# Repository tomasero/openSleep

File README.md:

# OpenSleep

The development of the hardware and software for this system started and most of it was done during my first semester at the Fluid Interfaces Group of the MIT Media Lab. This technology was used for many projects, [Dormio](https://www.media.mit.edu/projects/sleep-creativity/overview/) being the most notable. This project is part of a larger iniatiative called Engineering Dreams, which seeks to build technology that interfaces with the sleeping mind.

----

# The following is deprecated. We are about to release a new tutorial. Thanks for your patience!

----

## Hardware

### Components

| Qty | Value | Device  | Where |
|:---:|:-----:| -------:| ----- |
|  2  | .1uF  | CAP_CERAMIC0603 | Digikey: [399-1095-1-ND](https://www.digikey.com/product-detail/en/kemet/C0603C104K8RACTU/399-1095-1-ND/411370) |
|  1  |  1uF  | CAP_CERAMIC0603 | Digikey: [399-5090-1-ND](https://www.digikey.com/product-detail/en/kemet/C0603C105K4PACTU/399-5090-1-ND/1465624) | 
|  1  |  1K   | R-US_0503       | Digikey: [YAG1237CT-ND](https://www.digikey.com/product-detail/en/yageo/RT0603BRD071KL/YAG1237CT-ND/4340590) | 
|  2  | 100K  | R-US_R0603      | Digikey: [YAG1235CT-ND](https://www.digikey.com/product-detail/en/yageo/RT0603BRD07100KL/YAG1235CT-ND/4340588) |
|  3  |  1x2  | 1X2-SMD-HEADER  | Digikey: [S1113E-36-ND](https://www.digikey.com/product-detail/en/sullins-connector-solutions/GEC36SBSN-M89/S1113E-36-ND/862247) |
|  1  |  1x3  | 1X3-SMD-HEADER  | Digikey: [S1113E-36-ND](https://www.digikey.com/product-detail/en/sullins-connector-solutions/GEC36SBSN-M89/S1113E-36-ND/862247) |
|  1  |  1x5  | 1X5-SMD-HEADER  | Digikey: [S1113E-36-ND](https://www.digikey.com/product-detail/en/sullins-connector-solutions/GEC36SBSN-M89/S1113E-36-ND/862247) |
|  1  |       | RFD22301        | Digikey: [1562-1016-ND](https://www.digikey.com/product-detail/en/rf-digital-corporation/RFD22301/1562-1016-ND/5056363) |
|  1  | SPDT  | SLIDE-SWITCH    | Digikey: [401-2014-1-ND](https://www.digikey.com/product-detail/en/c-k/AYZ0103AGRLC/401-2014-1-ND/1640123) |
|  1  | Color | LED-1206-SMD    | Digikey: [516-1436-1-ND](https://www.digikey.com/product-detail/en/broadcom-limited/HSMR-C150/516-1436-1-ND/637760) |
|  1  |       | HR-SENSOR       | Adafruit: [1093](https://www.adafruit.com/product/1093) |
|  1  |       | FLEX-SENSOR     | Adafruit: [1070](https://www.adafruit.com/product/1070) |
|  2  |       | EDA-ELECTRODE-CABLE | [OpenBCI](https://shop.openbci.com/collections/frontpage/products/emg-ecg-snap-electrode-cables?variant=32372786958) |
| 2   |       | EDA-ELECTRODE   | [OpenBCI](https://shop.openbci.com/collections/frontpage/products/skintact-f301-pediatric-foam-solid-gel-electrodes-30-pack?variant=29467659395) |

### PCB

#### Design

##### Schematic

##### Layout 

#### Fabrication

You can either mill the PCB yourself using a CNC mill, or buy one from a PCB manufacturer.

##### Mill it

The original PCB for Doormio was made using a Roland MDX-20. All the PNG files used to mill the board can be found in the following folder:

    /hardware/PNG

##### Order it

[Oshpark!](https://oshpark.com/shared_projects/I6SkyNbt)

## Software

### Web App

Run the app:

    node web_app/app.js

Open the app:

    http://localhost:3000

### Mobile App

## Acknowledgements 

[Adam Horowitz](https://www.media.mit.edu/people/adamjhh/overview/) led the experiment design and execution to validate the system, [Oscar Rosello](https://www.media.mit.edu/people/rosello/overview/) the interaction and form factor, and  [Eyal Perry](https://www.media.mit.edu/people/eyalp/overview/) the iOS app development, signal processing and classification (and great mustache). [Matthew Ha](https://github.com/matthewha123) continued the development of the iOS 
    app and analysis of biosignals for sleep staging.

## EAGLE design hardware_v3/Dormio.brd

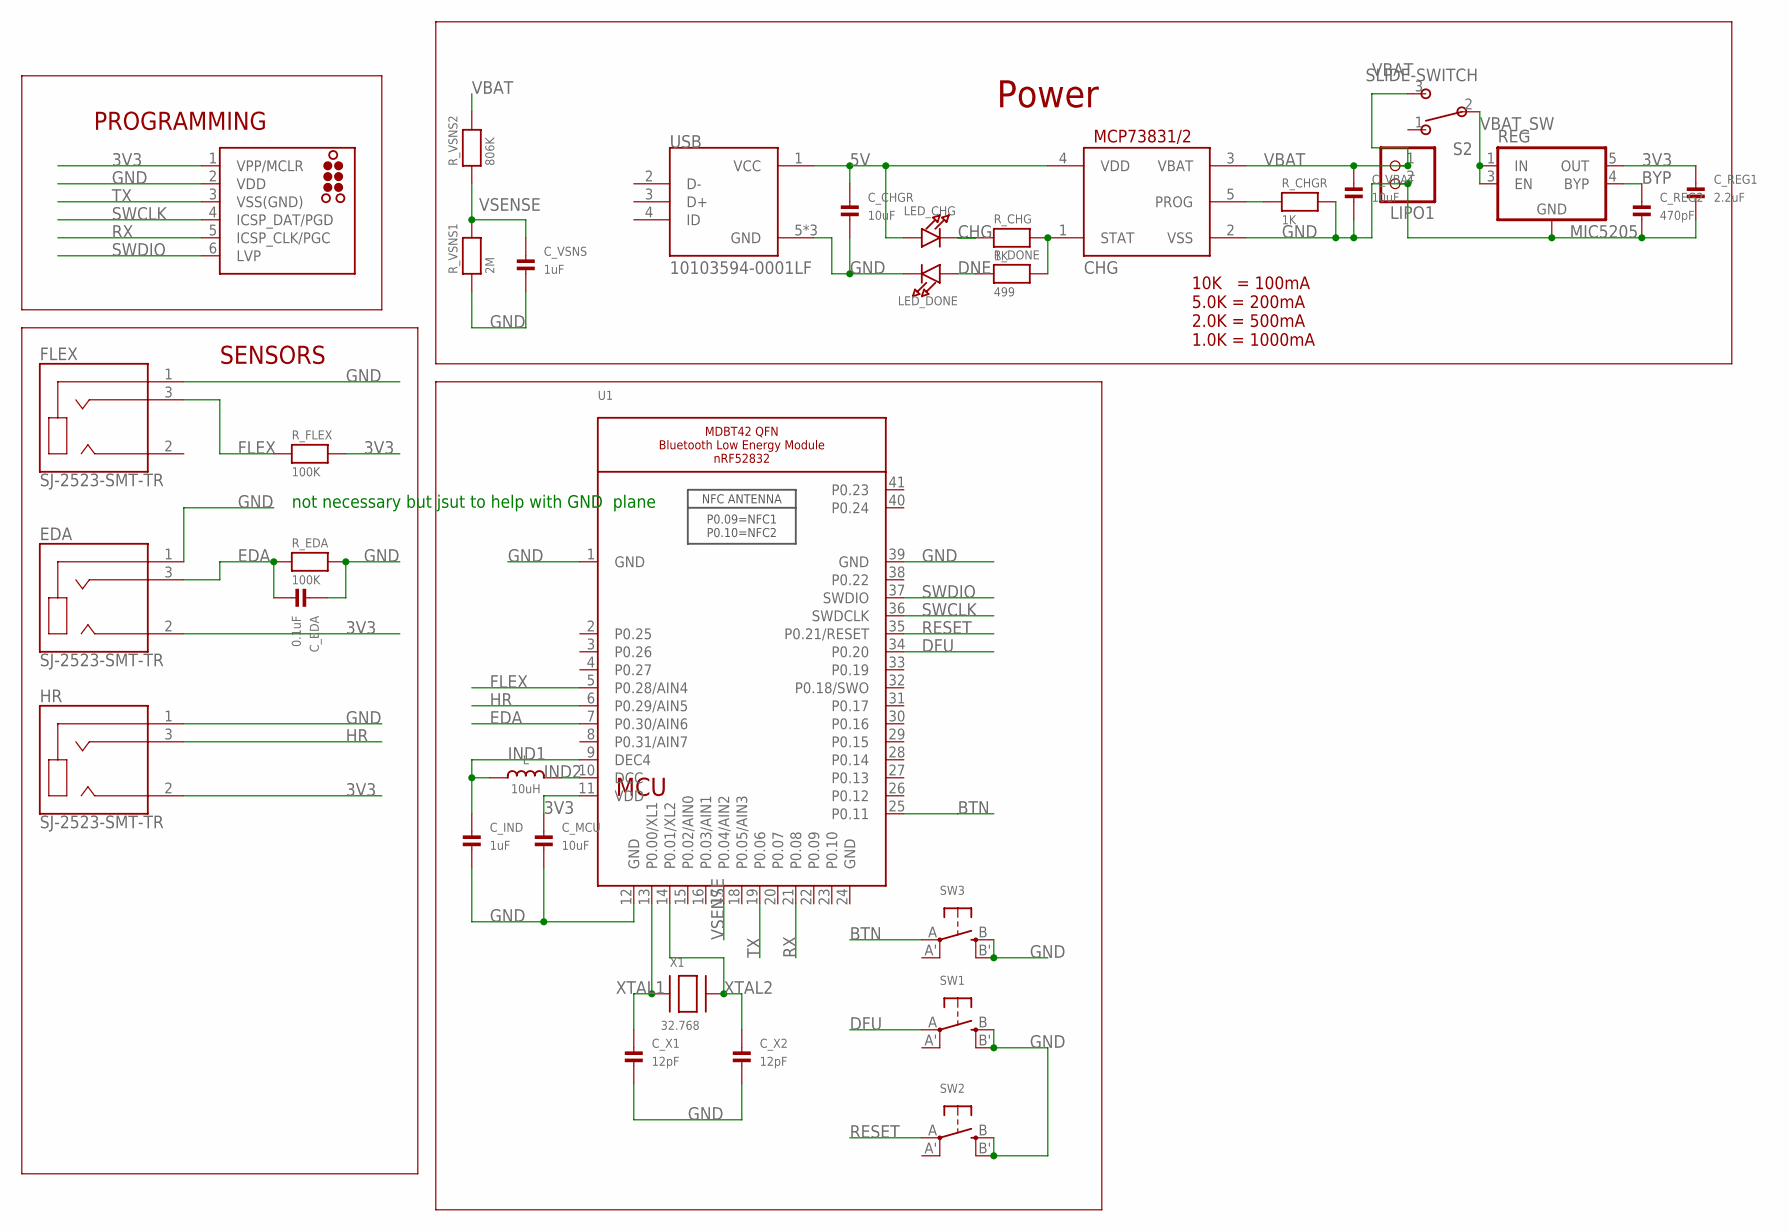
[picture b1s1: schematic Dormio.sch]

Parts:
CHG: MCP73831/OT; SOT23-5L
C_CHGR: 10uF; 1206
C_EDA: 0.1uF; 1206
C_IND: 1uF; 1206
C_MCU: 10uF; 1206
C_REG1: 2.2uF; 1206
C_REG2: 470pF; 1206
C_VBAT: 10uF; 1206
C_VSNS: 1uF; 1206
C_X1, C_X2: 12pF; 1206
EDA: SJ-2523-SMT-TR; CUI_SJ-2523-SMT-TR
FLEX: SJ-2523-SMT-TR; CUI_SJ-2523-SMT-TR
HR: SJ-2523-SMT-TR; CUI_SJ-2523-SMT-TR
J1: TC2030-MCP-NL
L: 10uH; MICROBUILDER_INDUCTOR_1007
LED_CHG: LED1206; CHIPLED_1206
LED_DONE: LED1206; CHIPLED_1206
LIPO1: JST_2PIN-SMT-RA; JST-PH-2-SMT-RA
REG: MIC5205; SOT23-5
R_CHG: 1K; 1206
R_CHGR: 1K; 1206
R_DONE: 499; 1206
R_EDA: 100K; 1206
R_FLEX: 100K; 1206
R_VSNS1: 2M; 1206
R_VSNS2: 806K; 1206
S2: SLIDE-SWITCH; AYZ0102AGRLC
SW1, SW2, SW3: MICROBUILDER_SWITCH_TACT_SMT4.6X2.8; MICROBUILDER_BTN_KMR2_4.6X2.8
U1: MICROBUILDER_NRF52832_MODULE_MDBT42; MICROBUILDER_BLE_MODULE_RAYTAC_MDBT42
USB: 10103594-0001LF; FCI_10103594-0001LF
X1: 32.768; XTAL3215

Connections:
3V3: C_MCU.1, C_REG1.1, EDA.2, HR.2, J1.1 (VPP/MCLR), REG.5 (OUT), R_FLEX.2, U1.11 (VDD)
5V: CHG.4 (VDD), C_CHGR.1, LED_CHG.A, USB.1 (VCC)
BTN: SW3.A, U1.25 (P0.11)
BYP: C_REG2.1, REG.4 (BYP)
CHG: LED_CHG.C, R_CHG.1
DFU: SW1.A, U1.34 (P0.20)
DNE: LED_DONE.A, R_DONE.1
EDA: C_EDA.2, EDA.3, R_EDA.1, U1.7 (P0.30/AIN6)
FLEX: FLEX.3, R_FLEX.1, U1.5 (P0.28/AIN4)
GND: CHG.2 (VSS), C_CHGR.2, C_EDA.1, C_IND.2, C_MCU.2, C_REG1.2, C_REG2.2, C_VBAT.2, C_VSNS.2, C_X1.2, C_X2.2, EDA.1, FLEX.1, HR.1, J1.2 (VDD), LED_DONE.C, LIPO1.2 (1), REG.2 (GND), R_CHGR.2, R_EDA.2, R_VSNS1.1, SW1.B (S), SW1.B' (S1), SW2.B (S), SW2.B' (S1), SW3.B (S), SW3.B' (S1), U1.1 (GND), U1.12 (GND), U1.39 (GND), USB.5 (GND), USB.P3 (GND), USB.P4 (GND)
HR: HR.3, U1.6 (P0.29/AIN5)
IND1: C_IND.1, L.P$1 (1), U1.9 (DEC4)
IND2: L.P$2 (2), U1.10 (DCC)
PROG: CHG.5 (PROG), R_CHGR.1
RESET: SW2.A, U1.35 (P0.21/RESET)
RX: J1.5 (ICSP_CLK/PGC), U1.21 (P0.08)
STAT: CHG.1 (STAT), R_CHG.2, R_DONE.2
SWCLK: J1.4 (ICSP_DAT/PGD), U1.36 (SWDCLK)
SWDIO: J1.6 (LVP), U1.37 (SWDIO)
TX: J1.3 (VSS(GND)), U1.19 (P0.06)
VBAT: CHG.3 (VBAT), C_VBAT.1, LIPO1.1 (2), R_VSNS2.2, S2.3
VBAT_SW: REG.1 (IN), REG.3 (EN), S2.2
VSENSE: C_VSNS.1, R_VSNS1.2, R_VSNS2.1, U1.17 (P0.04/AIN2)
XTAL1: C_X1.1, U1.13 (P0.00/XL1), X1.P$1
XTAL2: C_X2.1, U1.14 (P0.01/XL2), X1.P$2

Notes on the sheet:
MCU
SENSORS
PROGRAMMING
Power
10K = 100mA 5.0K = 200mA 2.0K = 500mA 1.0K = 1000mA
not necessary but jsut to help with GND plane

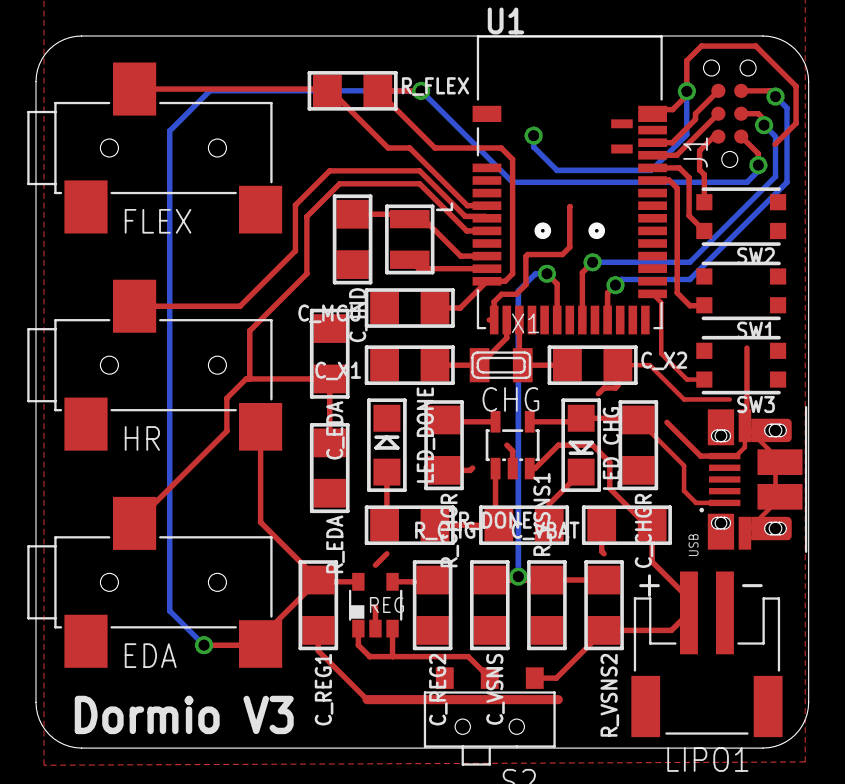
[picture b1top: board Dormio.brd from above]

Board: 2 copper layers, 42.6 x 39.2 mm, 34 parts (0 on the bottom side), 25 nets.

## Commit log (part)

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2017-11-26 graphing works
2017-11-26 graphing
2017-11-28 Experimental BPM
2017-11-28 merging
2017-12-26 adding hardare
2018-08-21 readme
2018-08-21 links to hardware
2018-10-28 updated app with mahalanobix distance
2018-11-02 Changed server flow to allow continuous upload
2018-11-04 changed config
2018-11-04 small timer change
2018-11-14 Changed feature from HR to RR, and changed from 0-1 to Mahalanobis
2018-11-15 New exp version
2018-11-16 added /data endpoint
2018-11-23 HBOSS
2018-11-26 First working version of the whole user flow, woohoooooo
2018-11-26 forgot a few PNGs
2018-12-01 user files
2018-12-01 added device UUID
2018-12-03 added multiple sessions support to the prediction server, still need to change the ios app to store datetime and post the device UUID
2018-12-05 git ignore for the data and models folders in prediciton server, tested the ios swift code with the new paramters for datetime and deviceUUID in the sleep api on local docker server, pending deployme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
2018-12-05 added endpoint for reporting cause of wakeup, possible bug: reports trigger twice because of how sleepDetected behaves, changes applied only to view controller rn
2018-12-12 now using server api url
2018-12-12 better naming for onset trigger
2018-12-13 checking for average power for silence detection
2018-12-13 added slight delay after end of recording
2018-12-13 added a calibration step for silence threshold.
2018-12-15 Refactored Code and Moved adding recordings to when the recording actually finishes. Other Misc thigns below: - Timer Invalidation and Label text moved to reset() function of viewController and reset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
2018-12-15 move changes from experiemental to flow view
2018-12-28 Added timer based dream catching to flow, added delete function to recordings table
2018-12-31 Added longpress on recording table row to share/upload
2019-01-06 Added alarm and alert when numOnsets is reached
2019-01-13 Renamed labels in storyboard, Added a minimum to max wait for onset time, added minimum recording time to dream recording
2019-01-13 Added function to Stop measuring from accelerometers when calibration is finished
2019-01-13 Added endpoint to retrieve triggers, added notebook to visualize data
2019-01-16 Experimental Mode start button disabled when parameters are empty
2019-01-16 Added info button in experiment view
2019-01-18 Added comments
2019-01-20 added code to present table view to record multiple sleep thinkof recordings
2019-01-21 Added delete functionality, boiler plate for moving rows - doesn't currently work
2019-01-22 Dynamically size table in thinkOf view, center and size the recording button in that view
2019-01-22 Added reordering function to thinkOfRecordingsTable
2019-01-22 Flow mode now supports the multiple sleep recordings, edit button now has title toggling between edit and done
2019-01-22 Added some more comments
2019-01-25 Added recording hboss in csv, endpoint to retrieve hboss, cells graphing min/max hboss
2019-01-25 Fixed prefix/suffix confusion
2019-01-25 Added false positive detection with flex
2019-01-25 fixed typo
2019-01-25 Added max time between flexes for false positive calculation, dash between prefix and uuid instaed of underscore
2019-01-27 Flex paramters for false positve and min/max recording times are now controlled in expreimental view
2019-01-27 Added function getInitParams(), sending all dormio settings to init api endpoint
2019-01-27 Added function to write the parameters to a file -- untested
2019-01-27 Added cell in visualize nb to print out session paramters
2019-01-27 Confirmed paramters file wrtign and endpoint work
2019-01-27 Flow view now gets the updated uuid with prefix from experimental view, fixed Bug causing dormio crash when disconnecting dormio on a view that does not have the connect button
2019-01-27 UNTESTED- data files are now nested twice- data/device_uuid/datetime/
2019-01-27 Fixed missing data folder bug
2019-01-27 Added some informational comments at the top
2019-02-01 Adding constraints to storyboard for compatibility with other iphones
2019-02-05 Added max time to first onset to experimental (tested) and flow(untested)
2019-02-08 Commented out speech detection functions, added prints for when recording has begun
2019-02-17 Debug prints in recordings for speech detection, enable/disable speech detection recording (for recording speech detected in between onsets) with switch on experiment screen
2019-02-17 ViewController now sends whether simulated data or speechdetection recording is on to the server
2019-02-19 remote server now returns json data instead of raw text
2019-02-19 fix annoying cors
2019-02-20 Basic webapp fetches data from remote webserver and stores in state
2019-02-20 Added canvas for graphing data
2019-02-20 getParams returns parameters in a json, visualize.ipynb is currently broken
2019-02-20 Commiting read only files
2019-02-20 Now rendering user and datetime input
2019-02-21 jsonify getUsers dict
2019-02-21 Datalists under dateInput fields now show all users and associated datetimes
2019-03-06 Website now handles data upload - has option to replace remote versions if uuid/datetime are the same
2019-03-06 Added info button
2020-04-15 images
2020-04-15 erasing myself
2020-04-15 cleaning lock.json
2020-04-15 Bump debug from 2.2.0 to 2.6.9 in /noble
    Bumps [debug](https://github.com/visionmedia/debug) from 2.2.0 to 2.6.9.
    - [Release notes](https://github.com/visionmedia/debug/releases)
    - [Changelog](https://github.com/visionmedia/debug/blob/2.6.9/CHANGELOG.md)
    - [Commits](https://github.com/visionmedia/debug/compare/2.2.0...2.6.9)
2020-04-15 Eyalo
2020-07-30 Update README.md
    Correct a typo in the Dormio project URL
2021-05-03 for gershon!
2022-01-15 Bump follow-redirects from 1.7.0 to 1.14.7 in /data_webapp
    Bumps [follow-redirects](https://github.com/follow-redirects/follow-redirects) from 1.7.0 to 1.14.7.
    - [Release notes](https://github.com/follow-redirects/follow-redirects/releases)
    - [Commits](https://github.com/follow-redirects/follow-redirects/compare/v1.7.0...v1.14.7)
    ---
    updated-dependencies:
    - dependency-name: follow-redirects
2022-02-03 merging embedded fixes for hw v3
2022-02-10 Bump ua-parser-js from 0.7.19 to 0.7.31 in /data_webapp
    Bumps [ua-parser-js](https://github.com/faisalman/ua-parser-js) from 0.7.19 to 0.7.31.
    - [Release notes](https://github.com/faisalman/ua-parser-js/releases)
    - [Commits](https://github.com/faisalman/ua-parser-js/compare/0.7.19...0.7.31)
    ---
    updated-dependencies:
    - dependency-name: ua-parser-js
2022-02-14 Bump ajv from 6.9.1 to 6.12.6 in /data_webapp
    Bumps [ajv](https://github.com/ajv-validator/ajv) from 6.9.1 to 6.12.6.
    - [Release notes](https://github.com/ajv-validator/ajv/releases)
    - [Commits](https://github.com/ajv-validator/ajv/compare/v6.9.1...v6.12.6)
    ---
    updated-dependencies:
    - dependency-name: ajv
2022-02-19 Bump url-parse from 1.4.4 to 1.5.7 in /data_webapp
    Bumps [url-parse](https://github.com/unshiftio/url-parse) from 1.4.4 to 1.5.7.
    - [Release notes](https://github.com/unshiftio/url-parse/releases)
    - [Commits](https://github.com/unshiftio/url-parse/compare/1.4.4...1.5.7)
    ---
    updated-dependencies:
    - dependency-name: url-parse
2022-02-27 Bump url-parse from 1.4.4 to 1.5.10 in /data_webapp
    Bumps [url-parse](https://github.com/unshiftio/url-parse) from 1.4.4 to 1.5.10.
    - [Release notes](https://github.com/unshiftio/url-parse/releases)
    - [Commits](https://github.com/unshiftio/url-parse/compare/1.4.4...1.5.10)
    ---
    updated-dependencies:
    - dependency-name: url-parse
2022-03-09 imporved UI - form doesnt pop out after 3 seconds and added a button to show session form
2022-03-09 fixed hide to show
2022-03-22 readme update
2022-03-22 Bump lodash from 4.17.11 to 4.17.21 in /deprecated/data_webapp
    Bumps [lodash](https://github.com/lodash/lodash) from 4.17.11 to 4.17.21.
    - [Release notes](https://github.com/lodash/lodash/releases)
    - [Commits](https://github.com/lodash/lodash/compare/4.17.11...4.17.21)
    ---
    updated-dependencies:
    - dependency-name: lodash
2022-03-22 Bump follow-redirects from 1.7.0 to 1.14.9 in /deprecated/data_webapp
    Bumps [follow-redirects](https://github.com/follow-redirects/follow-redirects) from 1.7.0 to 1.14.9.
    - [Release notes](https://github.com/follow-redirects/follow-redirects/releases)
    - [Commits](https://github.com/follow-redirects/follow-redirects/compare/v1.7.0...v1.14.9)
    ---
    updated-dependencies:
    - dependency-name: follow-redirects
2022-03-22 deleted lawinsider
2022-03-22 clean up
2022-06-01 Bump eventsource from 1.0.7 to 1.1.1 in /deprecated/data_webapp
    Bumps [eventsource](https://github.com/EventSource/eventsource) from 1.0.7 to 1.1.1.
    - [Release notes](https://github.com/EventSource/eventsource/releases)
    - [Changelog](https://github.com/EventSource/eventsource/blob/master/HISTORY.md)
    - [Commits](https://github.com/EventSource/eventsource/compare/v1.0.7...v1.1.1)
    ---
    updated-dependencies:
2022-12-07 Bump qs from 6.5.1 to 6.11.0 in /deprecated/noble
    Bumps [qs](https://github.com/ljharb/qs) from 6.5.1 to 6.11.0.
    - [Release notes](https://github.com/ljharb/qs/releases)
    - [Changelog](https://github.com/ljharb/qs/blob/main/CHANGELOG.md)
    - [Commits](https://github.com/ljharb/qs/compare/v6.5.1...v6.11.0)
    ---
    updated-dependencies:
2022-12-07 Bump express from 4.16.2 to 4.17.3 in /deprecated/noble
    Bumps [express](https://github.com/expressjs/express) from 4.16.2 to 4.17.3.
    - [Release notes](https://github.com/expressjs/express/releases)
    - [Changelog](https://github.com/expressjs/express/blob/master/History.md)
    - [Commits](https://github.com/expressjs/express/compare/4.16.2...4.17.3)
    ---
    updated-dependencies:
2022-12-10 Bump express from 4.16.4 to 4.18.2 in /deprecated/data_webapp
    Bumps [express](https://github.com/expressjs/express) from 4.16.4 to 4.18.2.
    - [Release notes](https://github.com/expressjs/express/releases)
    - [Changelog](https://github.com/expressjs/express/blob/master/History.md)
    - [Commits](https://github.com/expressjs/express/compare/4.16.4...4.18.2)
    ---
    updated-dependencies:
2022-12-31 Bump json5 and react-scripts in /deprecated/data_webapp
    Bumps [json5](https://github.com/json5/json5) to 2.2.3 and updates ancestor dependency [react-scripts](https://github.com/facebook/create-react-app/tree/HEAD/packages/react-scripts). These dependenci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
    Updates `json5` from 0.5.1 to 2.2.3
    - [Release notes](https://github.com/json5/json5/releases)
    - [Changelog](https://github.com/json5/json5/blob/main/CHANGELOG.md)
    - [Commits](https://github.com/json5/json5/compare/v0.5.1...v2.2.3)
    Updates `react-scripts` from 2.1.5 to 5.0.1
2023-01-11 Bump debug from 2.2.0 to 3.1.0 in /deprecated/noble
    Bumps [debug](https://github.com/debug-js/debug) from 2.2.0 to 3.1.0.
    - [Release notes](https://github.com/debug-js/debug/releases)
    - [Changelog](https://github.com/debug-js/debug/blob/3.1.0/CHANGELOG.md)
    - [Commits](https://github.com/debug-js/debug/compare/2.2.0...3.1.0)
    ---
    updated-dependencies:

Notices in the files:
parts and their libraries:
microbuilder: This work is placed in the public domain, and may be freely used for commercial and non-commercial work with the following conditions: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
tag-connect: ©2009 ROFA.cz - modified and updated by Robert Darlington ‹rdarlington@gmail.com›
